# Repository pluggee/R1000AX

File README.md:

JuicyBoard Robotics Platform
=======================
Overview
--------

This repository contains all PCB and firmware design resources for the R1000 robotics platform base boards and modules

File Structure
--------------
<pre>
(d) pcb	        : KiCAD PCB files
(d) firmware    : firmare for all modules
(d) doc         : documentation
(f) README.md   : Markdown README file
</pre>

Boards
------
Feature Boards
<pre>
R1000A 	        : Base Platform Board (2 variants, R1000AX and R1000A)
R1001		: Cascadable Stepper Motor Driver
R1002		: Quad 1A DC Low Side NFET Control Switches
R1003		: Analog/Digital I/O (Analog/Digital)
R1004		: Inertial Measurement Unit (IMU) Breakout
R1005		: General Purpose Breakout/Extension
R1006 		: SD Card
R1007		: Quad 20A DC Low Side NFET Control Switches
R1008		: Dual/Quad PT100 Platinum RTD temperature sensing module
</pre>
Adapters
<pre>
R1200		: Stepper Motor Master/Slave Bond
</pre>
Interposers
<pre>
R1100           : C.H.I.P. Pro Interposer with Host USB 2.0 and MicroSD
R1101           : particle.io photon Interposer
R1102           : particle.io electron Interposer
R1103           : Raspberry Pi data/power Interposer
</pre>
Special Boards
<pre>
R1000DBG	: Busy Bee Debug/Programming Board
</pre>
Setup Steps
-----------
Make sure to do the following before starting a project

1. Clone (or update) [KiCADLibs](https://github.com/pluggee/KiCADLibs) locally IN THE SAME DIRECTORY AS THIS REPO, this will include the required schematic symbols
2. Clone (or update) [pack3d](https://github.com/pluggee/pack3d) repo, this will include 3D models for PCB 3D view
3. Set KISYS3DMOD variable to point to your local **pack3d** repo, you can do this in the main KiCAD window by

**Preferences** -> **Configure Paths**

License
-------
R1000A board design files are released under the GNU GPL v3, which you can find at <http://www.gnu.org/licenses/gpl-3.0.en.html>,
Check License.md for more details.

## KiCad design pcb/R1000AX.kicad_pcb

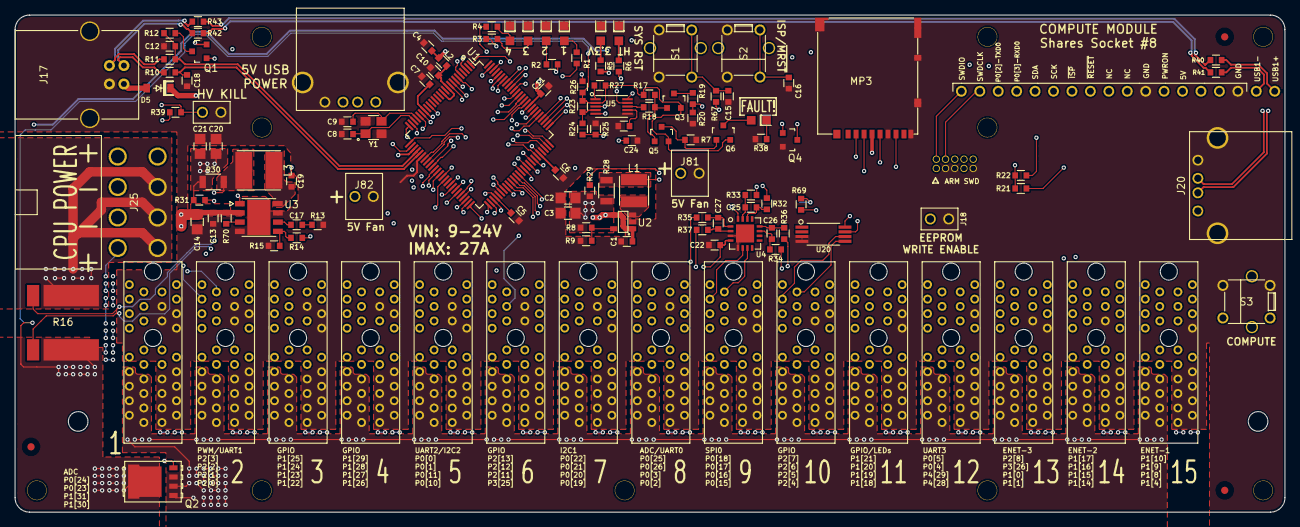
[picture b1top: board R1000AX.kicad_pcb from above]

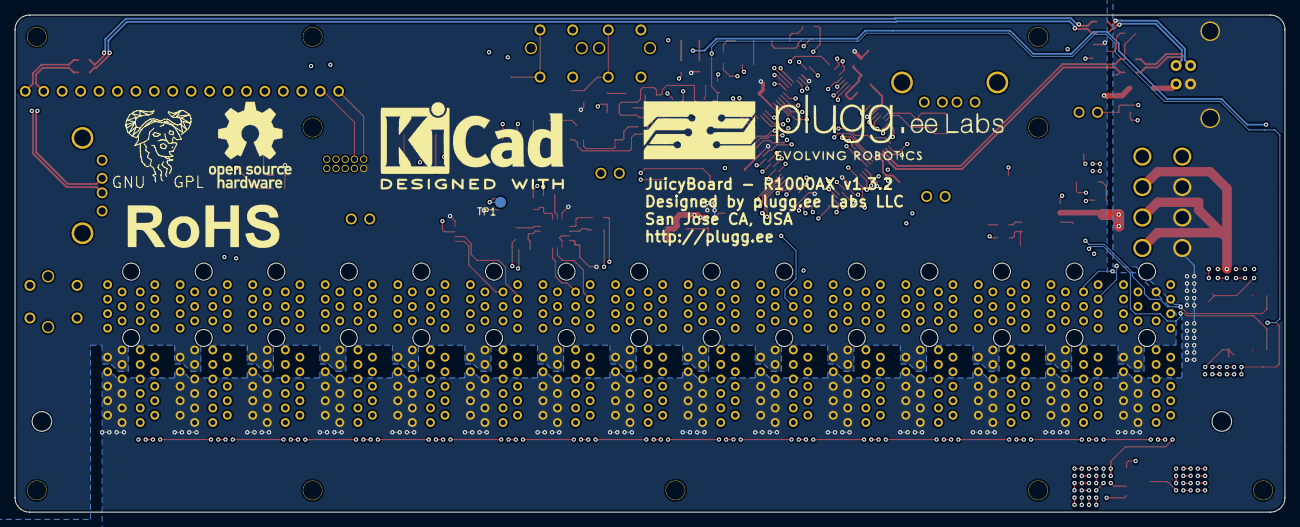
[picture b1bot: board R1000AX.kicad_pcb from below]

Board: 4 copper layers, 175.0 x 68.5 mm, 146 parts (6 on the bottom side), 134 nets.

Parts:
A1: ART; KiCad-Logo2_12mm_SilkScreen
A2: ART; pluggeeLabsLogo
A3: ART; OSHW-Logo_11.4x12mm_SilkScreen
A4: ART; Symbol_GNU-Logo_SilkscreenTop
A5: ART; RoHS-Logo_6mm_SilkScreen
C1: CC0603KRX5R5BB475; CAPC0603
C2, C3, C20, C21: CC0805MKX5R5BB226; CAPC0805
C4, C5, C6, C7, C10, C11, C13, C19, C22, C23, C25, C26, C27: CC0603KRX7R9BB104; CAPC0603
C8, C9: CC0603JRNPO9BN120; CAPC0603
C12, C18: CC0603JRNPO9BN180; CAPC0603
C14: CL21A475KLCLQNC; CAPC0805
C15, C16, C24: CC0603KRX7R9BB103; CAPC0603
C17: CC0603KRX7R9BB682; CAPC0603
D1: LTST-C171GKT; DIOC200X120X110
D2: LTST-C171TBKT; DIOC200X120X110
D5: MBR0520LT1G; SOD3717X135
DLED1, DLED2, DLED3, DLED4: LTW-170TK; DIOC200X120X110
DLED5: LTST-C171KRKT; DIOC200X120X110
FID1, FID2, FID3: FIDTOP001
J1, J2, J3, J4, J5, J6, J7, J8, J9, J10, J11, J12, J13, J14, J15: PCIESOCKET-X1
J16: CONN127P-02X05
J17: USB_B_RECEPTACLE
J18, J83: SOCKET254P-01X02; SOCKET254P-01X02_2
J19: COMPUTE_MOD_1
J20, J31: USB_A_RECEPTACLE
J25: SOCKET420P-02X04-CPU; SOCKET420P-02X04
J81, J82: SOCKET254P-01X02
L1: INDUCTOR_SRN4026-2R2Y; INDP400400X250
L2: 600Ohms; RESC0603
L3: INDUCTOR_SRN6045TA-4R7M; INDP600600X420
MP1, MP4, MP5, MP6, MP7, MP8, MP9, MP10, MP11, MP12: MECH_NPTH_M3
MP2: BRACKET-R1000AX
MP3: MICROSD_DM3AT-SF-PEJM5; MICROSD_RECEPTACLE_2
Q1: DMG2305UX-7; SOT190P290X130X100-3
Q2: PSMN1R2-30YLC; SOT127P500X110-5
Q3, Q5, Q6: Q_PNP_BEC; SOT190P290X130X100-3
Q4: Q_NPN_BEC; SOT190P290X130X100-3
R1, R2, R3, R4, R5: RC0603FR-071KL; RESC0603
R6, R27, R38: RC0603FR-072K21L; RESC0603
R7, R13, R17, R18, R19, R20, R21, R22, R67, R69: RC0603FR-0710KL; RESC0603
R8: RC0603FR-0727K4L; RESC0603
R9: RC0603FR-076K04L; RESC0603
R10, R11: RC0603FR-0733R2L; RESC0603
R12: RC0603FR-071K5L; RESC0603
R14: RC0603FR-0751K1L; RESC0603
R15: RC0603FR-079K76L; RESC0603
R16: RSENSE_WSL3637; RESC940914X064
R23, R26, R39, R70: RC0603FR-0766K5L; RESC0603
R24: RC0603FR-0711KL; RESC0603
R25: RC0603FR-076K49L; RESC0603
R28, R30: ERJ-8CWFR030V; RESC1206
R29, R31: RC0603FR-070RL; RESC0603
R32, R33, R34, R35, R36, R37: RC0603FR-077R5L; RESC0603
R40, R41, R42, R43: ERJ-3GEY0R00V; RESC0603
S1, S2, S3: SPST_PUSHBTN
TP1: TestPoint; TestPoint000
U1: LPC1769FBD100,551; QFP50P1400X1400X160-100
U2: AP3418; SOT095P300X150X145-5
U3: BD9E302EFJ-E2; SOP127P490X390X100-8NT320X240
U4: INA3221AIRGVR; QFN65P400X400X90-16NT210X210
U5: LM5060MM/NOPB; SOP50P300X300X100-10
U20: M24C08-FDW6TP; SOP65P440X300X120-8
Y1: XTAL4_12MHz; XTAL320X250X100

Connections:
3V3+: L1.2, R28.2, R33.2
3V3-: R29.2, R32.2
5V0+: L3.2, R30.2, R37.2
5V0-: R31.1, R35.2
+3V3: C2.1, C3.1, C4.1, C5.1, C6.1, C7.1, C11.1, C22.1, J1.B9, J1.B10, J1.B11, J2.B9, J2.B10, J2.B11, J3.B9, J3.B10, J3.B11, J4.B9, J4.B10, J4.B11, J5.B9, J5.B10, J5.B11, J6.B9, J6.B10, J6.B11, J7.B9, J7.B10, J7.B11, J8.B9, J8.B10, J8.B11, J9.B9, J9.B10, J9.B11, J10.B9, J10.B10, J10.B11, J11.B9, J11.B10, J11.B11, J12.B9, J12.B10, J12.B11, J13.B9, J13.B10, J13.B11, J14.B9, J14.B10, J14.B11, J15.B9, J15.B10, J15.B11, J16.1, L2.1, MP3.4, Q1.2, R5.1, R8.1, R21.1, R22.1, R28.1, R29.1, R67.2, R69.2, U1.19, U1.28, U1.42, U1.54, U1.71, U1.84, U1.96, U4.4, U4.16, U20.8
+5V: C1.1, C20.1, C21.1, D5.1, J1.A9, J1.A10, J1.A11, J2.A9, J2.A10, J2.A11, J3.A9, J3.A10, J3.A11, J4.A9, J4.A10, J4.A11, J5.A9, J5.A10, J5.A11, J6.A9, J6.A10, J6.A11, J7.A9, J7.A10, J7.A11, J8.A9, J8.A10, J8.A11, J9.A9, J9.A10, J9.A11, J10.A9, J10.A10, J10.A11, J11.A9, J11.A10, J11.A11, J12.A9, J12.A10, J12.A11, J13.A9, J13.A10, J13.A11, J14.A9, J14.A10, J14.A11, J15.A9, J15.A10, J15.A11, J19.4, J20.1, J31.1, J81.1, J82.1, R14.1, R30.1, R31.2, U2.1, U2.4
/COMPUTE_USB+: J19.18, J20.3, R40.1
/COMPUTE_USB-: J19.17, J20.2, R41.1
/EE_~WC: J18.1, R69.1, TP1.1, U20.7
/HV_EN_CONN: J25.8, R39.2
/IUSB_D+: R40.2, R43.1
/IUSB_D-: R41.2, R42.1
/MCU_USB_D+: C12.1, R11.2, R12.1, U1.29
/MCU_USB_D-: C18.1, R10.2, U1.30
/P2.9: Q1.1, U1.64
/PWRON: J19.5, S3.2
/Power/BOOT5V0: C19.1, U3.1
/Power/COMP5V0: C17.1, U3.6
/Power/FB3V3: R8.2, R9.1, U2.5
/Power/FB5V0: R14.2, R15.1, U3.5
/Power/SW3V3: L1.1, U2.3
/Power/SW5V0: C19.2, L3.1, U3.8
/PowerMonitor/IIN+: R16.3, R36.2
/PowerMonitor/IIN-: R16.4, R34.2
/PowerMonitor/IN+1: C26.1, R36.1, U4.12
/PowerMonitor/IN+2: C25.1, R33.1, U4.15
/PowerMonitor/IN+3: C27.1, R37.1, U4.2
/PowerMonitor/IN-1: C26.2, R34.1, U4.11
/PowerMonitor/IN-2: C25.2, R32.1, U4.14
/PowerMonitor/IN-3: C27.2, R35.1, U4.1
/PowerMonitor/LM5060_GATE: C24.1, Q2.4, U5.10
/PowerMonitor/LM5060_OVP: R24.2, R25.1, U5.3
/PowerMonitor/LM5060_SENSE: R27.1, U5.1
/PowerMonitor/LM5060_TIMER: C23.1, U5.7
/PowerMonitor/LM5060_UVLO: R23.2, R24.1, U5.4
/PowerMonitor/LM5060_~PGD: R18.2, U5.8
/TCK: J16.4, J19.15, U1.5
/TDO: J16.6, U1.1
/TMS: J16.2, J19.16, U1.3
/USB_5V+: D5.2, J17.1
/USB_D+: J17.3, R11.1, R43.2
/USB_D-: J17.2, R10.1, R42.2
/VDDA: C10.1, L2.2, U1.10, U1.12
/XTAL1: C9.1, U1.22, Y1.3
/XTAL2: C8.1, U1.23, Y1.1
/~RESET: C15.1, J19.9, R67.1, S1.2, U1.17
GND: C1.2, C2.2, C3.2, C4.2, C5.2, C6.2, C7.2, C8.2, C9.2, C10.2, C11.2, C12.2, C13.2, C14.2, C15.2, C16.2, C18.2, C20.2, C21.2, C22.2, C23.2, C24.2, D1.1, D2.1, DLED1.1, DLED2.1, DLED3.1, DLED4.1, J1.B1, J1.B2, J1.B3, J1.B4, J1.B5, J1.B6, J1.B7, J1.B8, J1.B12, J1.B13, J1.B14, J1.B15, J2.B1, J2.B2, J2.B3, J2.B4, J2.B5, J2.B6, J2.B7, J2.B8, J2.B13, J2.B14, J2.B15, J3.B1, J3.B2, J3.B3, J3.B4, J3.B5, J3.B6, J3.B7, J3.B8, J3.B12, J3.B14, J3.B15, J4.B1, J4.B2, J4.B3, J4.B4, J4.B5, J4.B6, J4.B7, J4.B8, J4.B14, J4.B15, J5.B1, J5.B2, J5.B3, J5.B4, J5.B5, J5.B6, J5.B7, J5.B8, J5.B12, J5.B13, J5.B15, J6.B1, J6.B2, J6.B3, J6.B4, J6.B5, J6.B6, J6.B7, J6.B8, J6.B13, J6.B15, J7.B1, J7.B2, J7.B3, J7.B4, J7.B5, J7.B6, J7.B7, J7.B8, J7.B12, J7.B15, J8.B1, J8.B2, J8.B3, J8.B4, J8.B5, J8.B6, J8.B7, J8.B8, J8.B15, J9.B1, J9.B2, J9.B3, J9.B4, J9.B5, J9.B6, J9.B7, J9.B8, J9.B12, J9.B13, J9.B14, J10.B1, J10.B2, J10.B3, J10.B4, J10.B5, J10.B6, J10.B7, J10.B8, J10.B13, J10.B14, J11.B1, J11.B2, J11.B3, J11.B4, J11.B5, J11.B6, J11.B7, J11.B8, J11.B12, J11.B14, J12.B1, J12.B2, J12.B3, J12.B4, J12.B5, J12.B6, J12.B7, J12.B8, J12.B14, J13.B1, J13.B2, J13.B3, J13.B4, J13.B5, J13.B6, J13.B7, J13.B8, J13.B12, J13.B13, J14.B1, J14.B2, J14.B3, J14.B4, J14.B5, J14.B6, J14.B7, J14.B8, J14.B13, J15.B1, J15.B2, J15.B3, J15.B4, J15.B5, J15.B6, J15.B7, J15.B8, J15.B12, J16.3, J16.5, J16.9, J17.4, J17.5, J18.2, J19.1, J19.6, J20.4, J20.5, J25.1, J25.2, J25.3, J31.4, J31.5, J81.2, J82.2, J83.2, MP3.6, MP3.SHLD, Q4.2, R7.2, R9.2, R13.2, R15.2, R20.2, R25.2, R38.2, S1.1, S2.1, S3.1, U1.11, U1.15, U1.31, U1.41, U1.55, U1.72, U1.83, U1.97, U2.2, U3.4, U3.7, U3.9, U4.3, U4.5, U4.17, U5.6, U20.3, U20.4, Y1.2, Y1.4
HT: C13.1, C14.1, J1.A1, J1.A2, J1.A3, J1.A4, J1.A5, J1.A6, J1.A7, J1.A8, J2.A1, J2.A2, J2.A3, J2.A4, J2.A5, J2.A6, J2.A7, J2.A8, J3.A1, J3.A2, J3.A3, J3.A4, J3.A5, J3.A6, J3.A7, J3.A8, J4.A1, J4.A2, J4.A3, J4.A4, J4.A5, J4.A6, J4.A7, J4.A8, J5.A1, J5.A2, J5.A3, J5.A4, J5.A5, J5.A6, J5.A7, J5.A8, J6.A1, J6.A2, J6.A3, J6.A4, J6.A5, J6.A6, J6.A7, J6.A8, J7.A1, J7.A2, J7.A3, J7.A4, J7.A5, J7.A6, J7.A7, J7.A8, J8.A1, J8.A2, J8.A3, J8.A4, J8.A5, J8.A6, J8.A7, J8.A8, J9.A1, J9.A2, J9.A3, J9.A4, J9.A5, J9.A6, J9.A7, J9.A8, J10.A1, J10.A2, J10.A3, J10.A4, J10.A5, J10.A6, J10.A7, J10.A8, J11.A1, J11.A2, J11.A3, J11.A4, J11.A5, J11.A6, J11.A7, J11.A8, J12.A1, J12.A2, J12.A3, J12.A4, J12.A5, J12.A6, J12.A7, J12.A8, J13.A1, J13.A2, J13.A3, J13.A4, J13.A5, J13.A6, J13.A7, J13.A8, J14.A1, J14.A2, J14.A3, J14.A4, J14.A5, J14.A6, J14.A7, J14.A8, J15.A1, J15.A2, J15.A3, J15.A4, J15.A5, J15.A6, J15.A7, J15.A8, Q2.1, Q2.2, Q2.3, R6.1, R70.1, U3.2, U5.9
HT_IN: J25.5, J25.6, J25.7, R16.1
HV_EN: J83.1, R26.2, R39.1, U5.5
HV_~PGD: J25.4, Q4.3
J01.PX1.A12.P0[24]: J1.A12, U1.8
J01.PX2.A13.P0[23]: J1.A13, U1.9
J01.PX3.A14.P1[31]: J1.A14, U1.20
J01.PX4.A15.P1[30]: J1.A15, U1.21
J02.PX1.A12.P2[3]: J2.A12, U1.70
J02.PX2.A13.P2[2]: J2.A13, U1.73
J02.PX3.A14.P2[1]: J2.A14, U1.74
J02.PX4.A15.P2[0]: J2.A15, U1.75
J03.PX1.A12.P1[25]: J3.A12, U1.39
J03.PX2.A13.P1[24]: J3.A13, U1.38
J03.PX3.A14.P1[23]: J3.A14, U1.37
J03.PX4.A15.P1[22]: J3.A15, U1.36
J04.PX1.A12.P1[29]: J4.A12, U1.45
J04.PX2.A13.P1[28]: J4.A13, U1.44
J04.PX3.A14.P1[27]: J4.A14, U1.43
J04.PX4.A15.P1[26]: J4.A15, U1.40
J05.PX1.A12.P0[0]: J5.A12, U1.46
J05.PX2.A13.P0[1]: J5.A13, U1.47
J05.PX3.A14.P0[11]: J5.A14, U1.49
J05.PX4.A15.P0[10]: J5.A15, U1.48
J06.PX1.A12.P2[13]: J6.A12, U1.50
J06.PX2.A13.P2[12]: J6.A13, U1.51
J06.PX3.A14.P2[11]: J6.A14, U1.52
J06.PX4.A15.P3[25]: J6.A15, U1.27
J07.PX1.A12.P0[22]: J7.A12, U1.56
J07.PX2.A13.P0[21]: J7.A13, U1.57
J07.PX3.A14.P0[20]: J7.A14, U1.58
J07.PX4.A15.P0[19]: J7.A15, U1.59
J08.PX1.A12.P0[25]: J8.A12, U1.7
J08.PX2.A13.P0[26]: J8.A13, U1.6
J08.PX3.A14.P0[3]: J8.A14, J19.13, U1.99
J08.PX4.A15.P0[2]: J8.A15, J19.14, U1.98
J09.PX1.A12.P0[18]: J9.A12, U1.60
J09.PX2.A13.P0[17]: J9.A13, U1.61
J09.PX3.A14.P0[16]: J9.A14, U1.63
J09.PX4.A15.P0[15]: J9.A15, U1.62
J10.PX1.A12.P2[7]: J10.A12, U1.66
J10.PX2.A13.P2[6]: J10.A13, U1.67
J10.PX3.A14.P2[5]: J10.A14, U1.68
J10.PX4.A15.P2[4]: J10.A15, U1.69
J11.PX1.A12.P1[21]: J11.A12, R4.1, U1.35
J11.PX2.A13.P1[20]: J11.A13, R3.1, U1.34
J11.PX3.A14.P1[19]: J11.A14, R2.1, U1.33
J11.PX4.A15.P1[18]: J11.A15, R1.1, U1.32
J12.PX1.A12.P0[5]: J12.A12, U1.80
J12.PX2.A13.P0[4]: J12.A13, U1.81
J12.PX3.A14.P4[29]: J12.A14, U1.85
J12.PX4.A15.P4[28]: J12.A15, U1.82
J13.PX1.A12.P2[8]: J13.A12, U1.65
J13.PX2.A13.P3[26]: J13.A13, U1.26
J13.PX3.A14.P1[0]: J13.A14, U1.95
J13.PX4.A15.P1[1]: J13.A15, U1.94
J14.PX1.A12.P1[17]: J14.A12, U1.86
J14.PX2.A13.P1[16]: J14.A13, U1.87
J14.PX3.A14.P1[15]: J14.A14, U1.88
J14.PX4.A15.P1[14]: J14.A15, U1.89
J15.PX1.A12.P1[10]: J15.A12, U1.90
J15.PX2.A13.P1[9]: J15.A13, U1.91
J15.PX3.A14.P1[8]: J15.A14, U1.92
J15.PX4.A15.P1[4]: J15.A15, U1.93
LV_EN: R70.2, U3.3
unnamed: C17.2, R13.1
unnamed: D1.2, R5.2
unnamed: D2.2, R6.2
unnamed: DLED1.2, R1.2
unnamed: DLED2.2, R2.2
unnamed: DLED3.2, R3.2
unnamed: DLED4.2, R4.2
unnamed: DLED5.1, R38.1
unnamed: DLED5.2, Q6.3
unnamed: Q1.3, R12.2
unnamed: Q3.1, Q5.1, R17.2, R18.1
unnamed: Q3.3, R19.1
unnamed: Q4.1, R19.2, R20.1
unnamed: Q5.3, Q6.1, R7.1
PFET_D: Q2.5, Q3.2, Q5.2, Q6.2, R16.2, R17.1, R23.1, R26.1, R27.2, U5.2
SCL0: J1.A16, J2.A16, J3.A16, J4.A16, J5.A16, J6.A16, J7.A16, J8.A16, J9.A16, J10.A16, J11.A16, J12.A16, J13.A16, J14.A16, J15.A16, J19.11, R21.2, U1.24, U4.6, U20.6
SDA0: J1.A17, J2.A17, J3.A17, J4.A17, J5.A17, J6.A17, J7.A17, J8.A17, J9.A17, J10.A17, J11.A17, J12.A17, J13.A17, J14.A17, J15.A17, J19.12, R22.2, U1.25, U4.7, U20.5
SD_MISO: MP3.7, U1.77
SD_MOSI: MP3.3, U1.76
SD_SCK: MP3.5, U1.78
SD_SSEL: MP3.2, U1.79
~MRESET: C16.1, J1.A18, J2.A18, J3.A18, J4.A18, J5.A18, J6.A18, J7.A18, J8.A18, J9.A18, J10.A18, J11.A18, J12.A18, J13.A18, J14.A18, J15.A18, J19.10, S2.2, U1.53

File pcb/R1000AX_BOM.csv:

Reference;Quantity;Value;Footprint;Datasheet;Manufacturer;MPN;SKU;Res;Tol;Pwr;C;Vmax;Type;Color
A1 ;1;ART;Symbols:KiCad-Logo2_12mm_SilkScreen;
A2 ;1;ART;pluggee:pluggeeLabsLogo;
A3 ;1;ART;Symbols:OSHW-Logo_11.4x12mm_SilkScreen;
A4 ;1;ART;Symbols:Symbol_GNU-Logo_SilkscreenTop;
A5 ;1;ART;Symbols:RoHS-Logo_6mm_SilkScreen;
C1 ;1;CC0603KRX5R5BB475;Main:CAPC0603;;Yageo;CC0603KRX5R5BB475;GENERIC;;±10%;;4.70 µF;6.3V;X5R;
C14 ;1;CL21A475KLCLQNC;Main:CAPC0805;;Samsung Electro-Mechanics America, Inc.;CL21A475KLCLQNC;GENERIC;;±10%;;4.70 µF;35V;X5R;
C15 C16 C24 ;3;CC0603KRX7R9BB103;Main:CAPC0603;;Yageo;CC0603KRX7R9BB103;GENERIC;;±10%;;10.0 nF;50.0V;X7R;
C17 ;1;CC0603KRX7R9BB682;Main:CAPC0603;;Yageo;CC0603KRX7R9BB682;GENERIC;;±10%;;6.80 nF;50.0V;X7R;
C12 C18 ;2;CC0603JRNPO9BN180;Main:CAPC0603;;Yageo;CC0603JRNPO9BN180;GENERIC;;±5%;;18.0 pF;50.0V;C0G/NP0;
C2 C20 C21 C3 ;4;CC0805MKX5R5BB226;Main:CAPC0805;;Yageo;CC0805MKX5R5BB226;GENERIC;;±20%;;22.0 µF;6.3V;X5R;
C10 C11 C13 C19 C22 C23 C25 C26 C27 C4 C5 C6 C7 ;13;CC0603KRX7R9BB104;Main:CAPC0603;;Yageo;CC0603KRX7R9BB104;GENERIC;;±10%;;100 nF;50.0;X7R;
C8 C9 ;2;CC0603JRNPO9BN120;Main:CAPC0603;;Yageo;CC0603JRNPO9BN120;GENERIC;;±5%;;12.0 pF;50.0V;C0G/NP0;
D1 ;1;LTST-C171GKT;Main:DIOC200X120X110;;Lite-On Inc.;LTST-C171GKT;STUFF;;;;;;;GREEN
D2 ;1;LTST-C171TBKT;Main:DIOC200X120X110;;Lite-On Inc.;LTST-C171TBKT;STUFF;;;;;;;BLUE
D5 ;1;MBR0520LT1G;Main:SOD3717X135;;ON Semiconductor;MBR0520LT1G;STUFF;;;;;;;
DLED1 DLED2 DLED3 DLED4 ;4;LTW-170TK;Main:DIOC200X120X110;;Lite-On Inc.;LTW-170TK;COMMON;;;;;;;WHITE
DLED5 ;1;LTST-C171KRKT;Main:DIOC200X120X110;;Lite-On Inc.;LTST-C171KRKT;STUFF;;;;;;;RED
FID1 FID2 FID3 ;3;FIDTOP001;Main:FIDTOP001;
J16 ;1;CONN127P-02X05;Main:CONN127P-02X05;;Sullins Connector Solutions;GRPB052VWVN-RC;DNI;;;;;;;
J17 ;1;USB_B_RECEPTACLE;Main:USB_B_RECEPTACLE;;On Shore Technology Inc.;USB-B1HSW6;GENERIC;;;;;;;
J19 ;1;COMPUTE_MOD_1;Main:COMPUTE_MOD_1;
J20 J31 ;2;USB_A_RECEPTACLE;Main:USB_A_RECEPTACLE;;Amphenol Commercial Products;UE27AC54100;STUFF;;;;;;;
J25 ;1;SOCKET420P-02X04-CPU;Main:SOCKET420P-02X04;;TE Connectivity AMP Connectors;1586042-8;GENERIC;;;;;;;
J1 J10 J11 J12 J13 J14 J15 J2 J3 J4 J5 J6 J7 J8 J9 ;15;PCIESOCKET-X1;Main:PCIESOCKET-X1;;Amphenol FCI;10018784-10200TLF;STUFF;;;;;;;
J81 J82 ;2;SOCKET254P-01X02;Main:SOCKET254P-01X02;;TE Connectivity AMP Connectors;640456-2;DNI;;;;;;;
J18 J83 ;2;SOCKET254P-01X02;Main:SOCKET254P-01X02_2;;Harwin Inc.;M20-9990246;GENERIC;;;;;;;
L1 ;1;INDUCTOR_SRN4026-2R2Y;Main:INDP400400X250;;Bourns Inc.;SRN4026-2R2Y;STUFF;;;;;;;
L2 ;1;600Ohms;Main:RESC0603;;Wurth Electronics Inc;742792651;GENERIC;;;;;;;
L3 ;1;INDUCTOR_SRN6045TA-4R7M;Main:INDP600600X420;;Bourns Inc.;SRN6045TA-4R7M;STUFF;;;;;;;
MP2 ;1;BRACKET-R1000AX;Main:BRACKET-R1000AX;
MP3 ;1;MICROSD_DM3AT-SF-PEJM5;Main:MICROSD_RECEPTACLE_2;;Hirose Electric Co Ltd;DM3AT-SF-PEJM5;STUFF;;;;;;;
MP1 MP10 MP11 MP12 MP4 MP5 MP6 MP7 MP8 MP9 ;10;MECH_NPTH_M3;Main:MECH_NPTH_M3;
Q1 ;1;DMG2305UX-7;Main:SOT190P290X130X100-3;;Diodes Incorporated;DMG2305UX-7;STUFF;;;;;;;
Q2 ;1;PSMN1R2-30YLC;Main:SOT127P500X110-5;;NXP Semiconductors;PSMN1R2-30YLC,115;STUFF;;;;;;;
Q3 Q5 Q6 ;3;Q_PNP_BEC;Main:SOT190P290X130X100-3;;ON Semiconductor;MMBT4403LT3G;STUFF;;;;;;;
Q4 ;1;Q_NPN_BEC;Main:SOT190P290X130X100-3;;ON Semiconductor;MMBT2222ALT3G;STUFF;;;;;;;
R1 R2 R3 R4 R5 ;5;RC0603FR-071KL;Main:RESC0603;;Yageo;RC0603FR-071KL;GENERIC;1.00 kΩ;±1%;100 mW;;;;
R10 R11 ;2;RC0603FR-0733R2L;Main:RESC0603;;Yageo;RC0603FR-0733R2L;GENERIC;33.2 Ω;±1%;100 mW;;;;
R12 ;1;RC0603FR-071K5L;Main:RESC0603;;Yageo;RC0603FR-071K5L;GENERIC;1.50 kΩ;±1%;100 mW;;;;
R14 ;1;RC0603FR-0751K1L;Main:RESC0603;;Yageo;RC0603FR-0751K1L;GENERIC;51.1 kΩ;±1%;100 mW;;;;
R15 ;1;RC0603FR-079K76L;Main:RESC0603;;Yageo;RC0603FR-079K76L;GENERIC;9.76 kΩ;±1%;100 mW;;;;
R16 ;1;RSENSE_WSL3637;Main:RESC940914X064;;Vishay Dale;WSL36373L000FEA;STUFF;;;;;;;
R24 ;1;RC0603FR-0711KL;Main:RESC0603;;Yageo;RC0603FR-0711KL;GENERIC;11.0 kΩ;±1%;100 mW;;;;
R25 ;1;RC0603FR-076K49L;Main:RESC0603;;Yageo;RC0603FR-076K49L;GENERIC;6.49 kΩ;±1%;100 mW;;;;
R28 R30 ;2;ERJ-8CWFR030V;Main:RESC1206;;Panasonic Electronic Components;ERJ-8CWFR030V;GENERIC;0.03 Ω;±1%;1 W;;;;
R29 R31 ;2;RC0603FR-070RL;Main:RESC0603;;Yageo;RC0603FR-070RL;GENERIC;0.00 Ω;±1%;100 mW;;;;
R32 R33 R34 R35 R36 R37 ;6;RC0603FR-077R5L;Main:RESC0603;;Yageo;RC0603FR-077R5L;GENERIC;7.50 Ω;±1%;100 mW;;;;
R23 R26 R39 R70 ;4;RC0603FR-0766K5L;Main:RESC0603;;Yageo;RC0603FR-0766K5L;GENERIC;66.5 kΩ;±1%;100 mW;;;;
R40 R41 R42 R43 ;4;ERJ-3GEY0R00V;Main:RESC0603;;Panasonic Electronic Components;ERJ-3GEY0R00V;DNI;0.00 Ω;±1%;100 mW;;;;
R27 R38 R6 ;3;RC0603FR-072K21L;Main:RESC0603;;Yageo;RC0603FR-072K21L;GENERIC;2.21 kΩ;±1%;100 mW;;;;
R13 R17 R18 R19 R20 R21 R22 R67 R69 R7 ;10;RC0603FR-0710KL;Main:RESC0603;;Yageo;RC0603FR-0710KL;GENERIC;10.0 kΩ;±1%;100 mW;;;;
R8 ;1;RC0603FR-0727K4L;Main:RESC0603;;Yageo;RC0603FR-0727K4L;GENERIC;27.4 kΩ;±1%;100 mW;;;;
R9 ;1;RC0603FR-076K04L;Main:RESC0603;;Yageo;RC0603FR-076K04L;GENERIC;6.04 kΩ;±1%;100 mW;;;;
S1 S2 S3 ;3;SPST_PUSHBTN;Main:SPST_PUSHBTN;;TE Connectivity Alcoswitch Switches;1825027-5;STUFF;;;;;;;
TP1 ;1;TestPoint;Main:TestPoint000;
U1 ;1;LPC1769FBD100,551;Main:QFP50P1400X1400X160-100;;NXP Semiconductors;LPC1769FBD100,551;STUFF;;;;;;;
U2 ;1;AP3418;Main:SOT095P300X150X145-5;;Diodes Incorporated;AP3418KTR-G1;STUFF;;;;;;;
U20 ;1;M24C08-FDW6TP;Main:SOP65P440X300X120-8;;STMicroelectronics;M24C08-FDW6TP;STUFF;;;;;;;
U3 ;1;BD9E302EFJ-E2;Main:SOP127P490X390X100-8NT320X240;;Rohm Semiconductor;BD9E302EFJ-E2;STUFF;;;;;;;
U4 ;1;INA3221AIRGVR;Main:QFN65P400X400X90-16NT210X210;;Texas Instruments;INA3221AIRGVR;STUFF;;;;;;;
U5 ;1;LM5060MM/NOPB;Main:SOP50P300X300X100-10;;Texas Instruments;LM5060MM/NOPB;STUFF;;;;;;;
Y1 ;1;XTAL4_12MHz;Main:XTAL320X250X100;;Abracon LLC;ABM8G-12.000MHZ-4Y-T3;STUFF;;;;;;;

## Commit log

2016-07-03 moved from R1000 repo
2016-07-09 added 4 pin board to wire
2016-07-11 wip, added 3.3V reg
2016-07-12 added sheet for MCU pin mapping
2016-07-14 connected nets between MCU and connectors
2016-07-14 wip, 90% sch complete
2016-07-16 completed schematics
2016-07-17 layout wip
2016-07-17 wip, cleaned routing to retoute MCU prioritized
2016-07-19 layout wip, need to plan mechanical and lug placement
2016-07-21 tagging to remove lugs
2016-07-22 layout wip, need to resolve USB ports mix up
2016-07-22 wip: layout complete, need to complete markings
2016-07-23 completed v1.0
2016-07-23 added logo pic
2016-07-23 added gerbers
2016-07-25 updated readme with all PCB versions;
2016-07-25 corrected 1002 to 1002A
2016-07-26 regenerated gerbers after fixing silk screen, adding P1.1
2016-07-30 corrected 50A to 20A
2016-07-30 releasing 1.0.2b, added USB softconnect structure and fixed silkscreen
2016-08-02 releasding v1.0.3b, modifications for manufacturability
2016-08-19 added BOM
2016-09-22 wip, version 1.1
2016-09-22 updated pinlist with V1.1, wip
2016-09-23 wip, routed all slots
2016-09-24 wip, submitted first placement review
2016-09-28 wip, completed a round of placement, mini board is 122mm x 65mm
2016-09-29 releasing v1.1.0
2016-09-29 wip, replaced type-B with mini type-B
2016-09-30 wip, added silk screen notes
2016-10-02 created bbox 3d model of board
2016-10-02 updated pinlist, sorted pins in scrap tab
2016-10-03 cleaned up silk screen
    moved microSD to top layer and expanded the board a little to the right
2016-10-03 cleaned up with full SD card receptacle
2016-10-03 fixed one more silk screen
2016-10-04 added slot numbers in silk screen
2016-10-04 removed date tagged gerbers directories
2016-10-04 exported and verified gerbers
2016-10-05 fixed led trace connections to allow easier reduction to 10 slot
2016-10-05 updated BOM
2016-10-05 changed C14 to 0805
2016-10-06 removed hanging unconnected nets
2016-10-09 fixed RPi footprint
2016-10-12 added powermon sheet
2016-10-13 completed layout, still need to finalize resistor values (no new netlist)
2016-10-13 updated gerbers
2016-10-13 updated layout and gerbers, moved C24 from under the bracket
2016-10-13 added mode thermal vias to FET source
2016-10-14 added legend text file for layer descriptions
2016-10-21 added gitignore
2016-10-27 added lm5060 calculation sheet
2016-10-28 updated calculations from datasheet
2016-11-01 updated and verified LM5060 calculations vs measurements
2016-11-02 updated bom files
2016-11-02 removed UART header, moved LEDs to front, wip
2016-11-02 wip, performing 1.1.1 fixes
2016-11-03 wip, need to add sense resistors for supplies
2016-11-29 updated pin map with swapping ISP0 and MRESET
2016-11-29 added BOM and illustration files
2016-11-29 added illustration files
2016-11-29 wip, adding to git
2016-11-29 added .gitignore
2016-11-29 added R1008 to readme
2016-12-12 now ISP and MRESET have the same function in schematics
2016-12-12 updated pinlist, MRESET and ISP0 are the same function now, this prevents interrupting any of the modules if the user pushes ISP0 button
2016-12-12 cleaned layout and ready for 1.2.0 release, need to finalize checks
2016-12-13 added 5V fans and kill switch
2016-12-14 added low voltage kill switch with option to track hv kill, or keep LV on all the time. improved ground path from connector, re-exported gerbers for release
2016-12-14 cleaned up floating net 0
2016-12-14 updated xlsx doc
2016-12-22 updated xlsx BOM file
2016-12-23 cleaned up BOM
2016-12-23 added position files
2016-12-25 added fiducials and re-laid ground and high tension planes
2016-12-29 fixed dfm orientation for L3
2016-12-29 wip, added eeprom and test point for write protecting ROM during normal operation
2016-12-29 wip, adding eeprom
2017-01-11 updating BOM
2017-01-11 updated BOM generation with semi-colons isntead of comas
2017-01-11 changed csv separator to ;
2017-02-02 added license info in readme
2017-02-02 a little cleanup, still need to write a guide for setting up design with kicad
2017-02-23 updated LM5060 calculations and restored pin map
2017-02-23 wip, tagging
2017-02-23 updated gitignore
2017-03-23 wip, need to correct footprints
2017-03-23 completed schematics, layout is clean
2017-03-24 generated gerbers for review
2017-03-24 updated doc
2017-03-24 added release notes
2017-03-24 renamed files to match R1000AX, cleaned up, re-plotted gerbers, generated schematics PDF
2017-03-27 updated silkscreen with RoHS
2017-03-29 added position files for SMT assembly
2017-03-30 added socket for CHIP and other compute modules
2017-03-31 completed layout with internet connected module, updated gerbers and bom
2017-03-31 ensured distance margin between last module and host usb connector
2017-03-31 updated schematic pdf
2017-03-31 exported position files
2017-03-31 regenerated BOM with new script that groups components
2017-04-01 completed v1.3.1, implemented changes based on second crowdsupply update
2017-04-01 re-exported
2017-04-02 added host USB to LPC USB jump option using a diffpair
2017-04-03 updated with interposer board numbers
2017-04-04 fixed 3d model
2017-04-04 added CAD files
2017-04-04 moved SD card more towards edge, making it accessible from case
2017-04-06 re-exported gerbers, moved SD card towards edge
2017-04-06 fixed dimensions for tactile switches
2017-04-06 updated SPST BOM to lateral switch
2017-04-06 connected swd to compute
2017-04-07 upated schematics
2017-04-07 added sheet for documentation
2017-04-10 added mounting holes for ubiquity robotics
2017-04-11 replaced molex USB connector with a common connector, all USBs are low profile now
2017-04-11 fixed c7 location
2017-04-11 refreshed J19
2017-04-14 ready for 1.3.2 crowdsupply release
2017-08-23 removed R1201 and R1203
2017-08-23 added R1103, RPi interposer
